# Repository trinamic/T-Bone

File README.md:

T-Bone
======
Electronic for up to 5 axes DIY desktop manufacturing platforms

LICENSE Files
=============
"LICENSE_HW" --> Attribution-ShareAlike 4.0 International license effective for the hardware part
"LICENSE_SW" --> agpl-3.0 license effective for the software part

"Software/ArduinoClient" Folder
===============================
The ArduinoClient folder  contains the Arduino software.

"Documentation/SoftwareDocumentation.pdf" File
==============================================
Documentation for the implemented protocol to communicate with the T-Bone via the UART interface.

"Documentation/T-bone_command_documentation.txt" File
=====================================================
Example file for the communication between Beagle Bone Black and the T-Bone (Arduino Leonardo)

Arduino Leonardo Pinout
=======================
Adapted from pins.h in the Arduino software.

Arduino Pin – Atmel Pin & function - connection

    D0 - PD2, RXD1/INT2 - Serial BeagleBone (UART1_TXD)
    D1 - PD3 TXD1/INT3 - Serial BeagleBone (UART1_RXD)
    D2 - PD1 SDA SDA/INT1 - Interrupt 4361 Nr.2
    D3# - PD0 PWM8/SCL OC0B/SCL/INT0 - Interrupt 4361 Nr.1
    D4 - A6 - PD4 ADC8 - CS 4361 Nr. 1
    D5# - PC6 ??? OC3A/#OC4A - PWM3, Fan
    D6# A7 - PD7 FastPWM #OC4D/ADC10 - CS 5031 Nr. 3
    D7 - PE6 INT6/AIN0 - Interrupt 4361 Nr.3
    D8 A8 - PB4 ADC11/PCINT4 - Interrupt 5041
    D9# A9 - PB5 PWM16 OC1A/#OC4B/ADC12/PCINT5 - PWM 1
    D10# A10 - PB6 PWM16 OC1B/0c4B/ADC13/PCINT6 - PWM 2
    D11# - PB7 PWM8/16 0C0A/OC1C/#RTS/PCINT7 - CS 5041
    D12 A11 - PD6 T1/#OC4D/ADC9 - CS 4361 Nr. 2
    D13# - PC7 PWM10 CLK0/OC4A - clock output do not use, never!
    A0 - D18 PF7 ADC7 - Temperature Sensor 1
    A1 - D19 PF6 ADC6 - Temperature Sensor 2
    A2 - D20 PF5 ADC5 - Temperature Sensor 3
    A3 - D21 PF4 ADC4 - Start Signal
    A4 - D22 PF1 ADC1 - Current PWM 1
    A5 - D23 PF0 ADC0 - Current PWM 2
    MISO - D14 PB3 MISO,PCINT3 - MISO
    SCK - D15 PB1 SCK,PCINT1 - SCK
    MOSI - D16 PB2 MOSI,PCINT2 - MOSI
    SS - D17 PB0 RXLED,SS/PCINT0 - RX LED
    TXLED - PD5 . TX LED
    HWB - PE2 HWB - Reset for motion drivers

"Software/ArduinoLibraries" Folder
==================================
This folder contains the used Arduino Libraries needed to compile the code.
!!Attention!!
The used libraries are standard ones, BUT customized. So be sure to use these!
!!Attention!!

For information on installing libraries, see: http://arduino.cc/en/Guide/Libraries

"Software/t_bone_server" Folder
===============================
This folder contains the software running on the Beagle Bone Black for the Deluxe version.

It's prepared to run a 3D-Printer Hardware. But can be customized to control different kind of desktop manufacturing platforms.

"Hardware/T-Bone Folder"
========================
Contains schematic and board design of the latest version of the T-Bone HW

"Hardware/Programming board" Folder
===================================
Contains schematic of a programming board adapter

"Hardware/BBQ" Folder
=====================
Contains schematic and board design for BBQ breakout board to evaluate TMC chipsets

"Hardware/TMC2100" Folder
=========================
Contains startup instructions for TMC2100 breakout board and schematics + board design

LJ

The T-Bone Team
2014

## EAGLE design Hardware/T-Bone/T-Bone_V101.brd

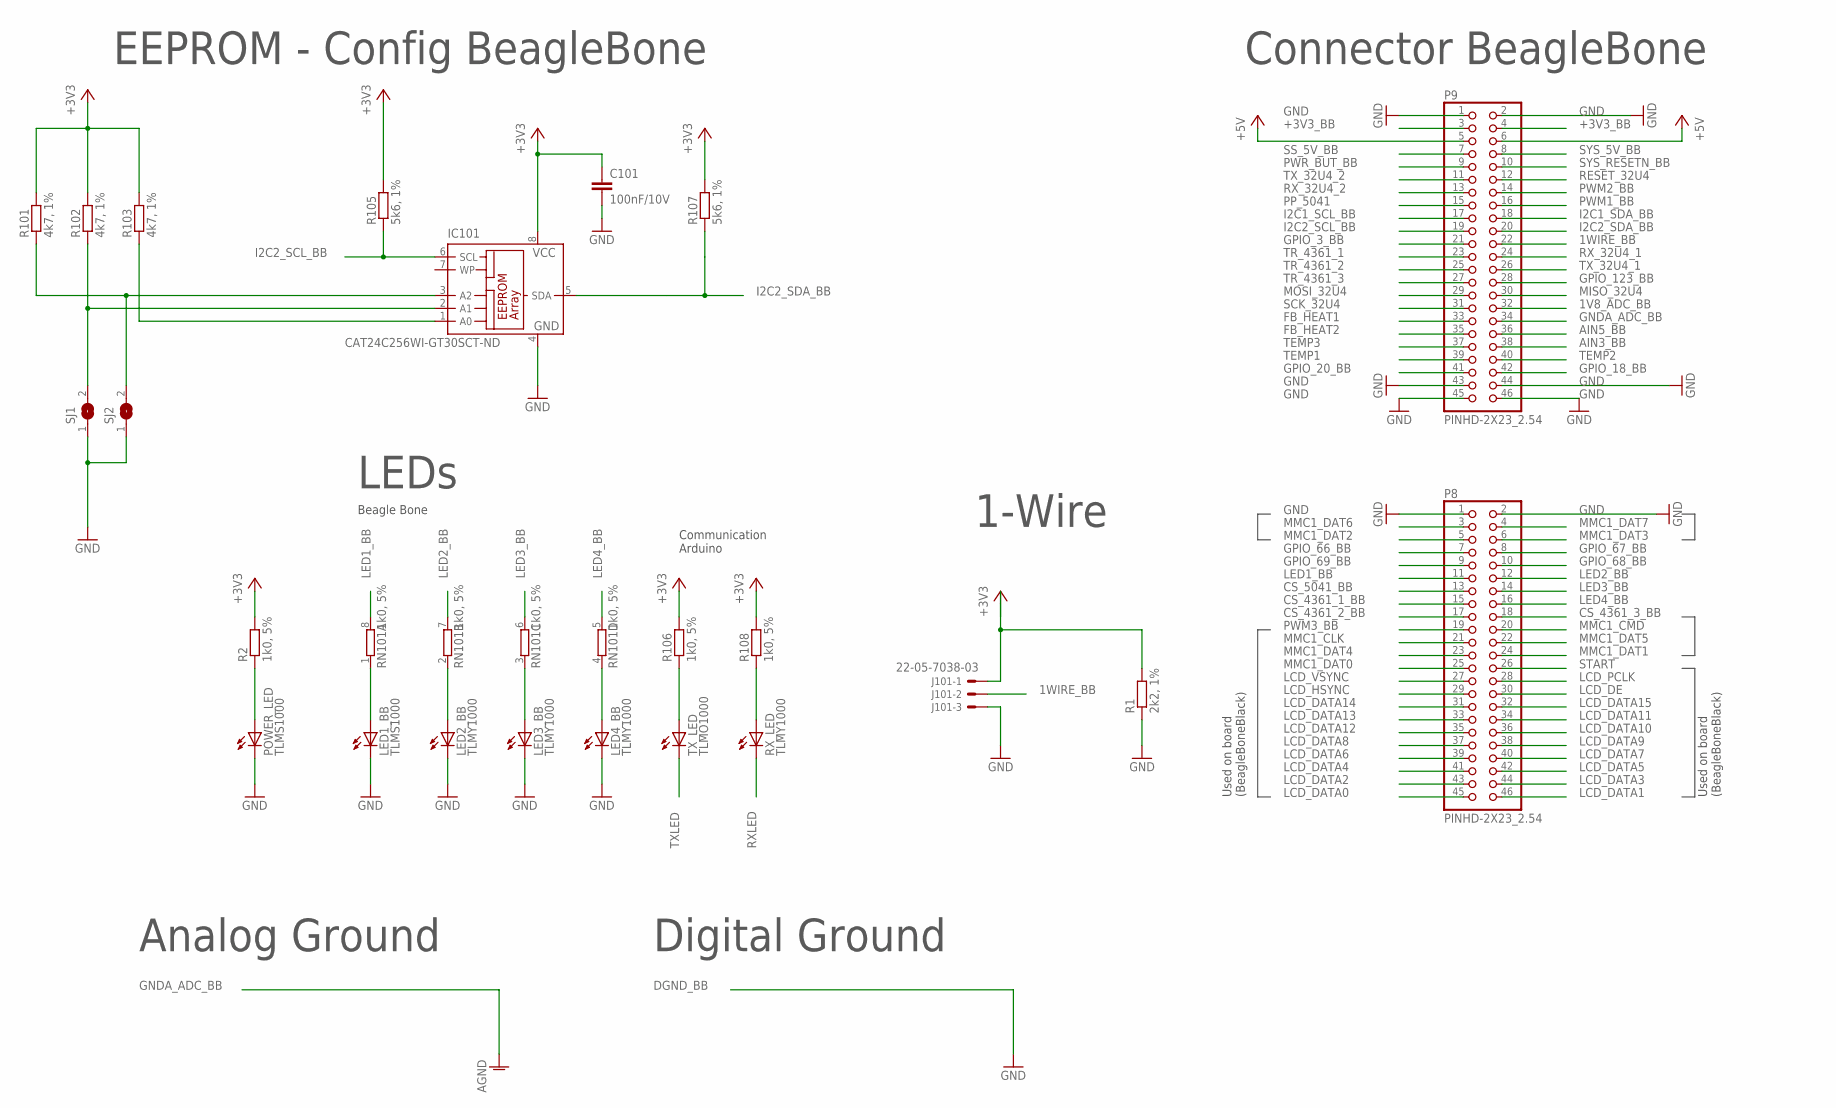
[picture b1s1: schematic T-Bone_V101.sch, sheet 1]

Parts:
C101: 100nF/10V; C0402K
IC101: CAT24C256WI-GT30SCT-ND; SO-08
J101: 22-05-7038-03; 7395-03
LED1_BB: TLMS1000; CHIP-LED0603
LED2_BB, LED3_BB, LED4_BB: TLMY1000; CHIP-LED0603
P8, P9: PINHD-2X23_2.54; 2X23
POWER_LED: TLMS1000; CHIP-LED0603
R1: 2k2, 1%; R0603
R2, R106, R108: 1k0, 5%; R0402
R101, R102, R103: 4k7, 1%; R0402
R105, R107: 5k6, 1%; R0402
RN101: 1k0, 5%; YC124
RX_LED: TLMY1000; CHIP-LED0603
SJ1, SJ2: SJ
TX_LED: TLMO1000; CHIP-LED0603

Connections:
1V8_ADC_BB: P9.32; also elsewhere on the board
1WIRE_BB: J101.2, P9.22
+3V3: C101.1, IC101.8 (VCC), J101.1, R1.2, R2.2, R101.2, R102.2, R103.2, R105.2, R106.2, R107.2, R108.2; also elsewhere on the board
+3V3_BB: P9.3, P9.4
+5V: P9.5, P9.6; also elsewhere on the board
AIN3_BB: P9.38
AIN5_BB: P9.36
CS_4361_1_BB: P8.15; also elsewhere on the board
CS_4361_2_BB: P8.17; also elsewhere on the board
CS_4361_3_BB: P8.18; also elsewhere on the board
CS_5041_BB: P8.13; also elsewhere on the board
FB_HEAT1: P9.33; also elsewhere on the board
FB_HEAT2: P9.35; also elsewhere on the board
GND: C101.2, IC101.4 (GND), J101.3, LED1_BB.C, LED2_BB.C, LED3_BB.C, LED4_BB.C, P8.1, P8.2, P9.1, P9.2, P9.43, P9.44, P9.45, P9.46, POWER_LED.C, R1.1, SJ1.1, SJ2.1; also elsewhere on the board
GNDA_ADC_BB: P9.34
GPIO_3_BB: P9.21
GPIO_18_BB: P9.42
GPIO_20_BB: P9.41
GPIO_66_BB: P8.7
GPIO_67_BB: P8.8
GPIO_68_BB: P8.10
GPIO_69_BB: P8.9
GPIO_123_BB: P9.28
I2C1_SCL_BB: P9.17
I2C1_SDA_BB: P9.18
I2C2_SCL_BB: IC101.6 (SCL), P9.19, R105.1
I2C2_SDA_BB: IC101.5 (SDA), P9.20, R107.1
LCD_DATA0: P8.45
LCD_DATA1: P8.46
LCD_DATA2: P8.43
LCD_DATA3: P8.44
LCD_DATA4: P8.41
LCD_DATA5: P8.42
LCD_DATA6: P8.39
LCD_DATA7: P8.40
LCD_DATA8: P8.37
LCD_DATA9: P8.38
LCD_DATA10: P8.36
LCD_DATA11: P8.34
LCD_DATA12: P8.35
LCD_DATA13: P8.33
LCD_DATA14: P8.31
LCD_DATA15: P8.32
LCD_DE: P8.30
LCD_HSYNC: P8.29
LCD_PCLK: P8.28
LCD_VSYNC: P8.27
LED1_BB: P8.11, RN101.8 (2)
LED2_BB: P8.12, RN101.7 (2)
LED3_BB: P8.14, RN101.6 (2)
LED4_BB: P8.16, RN101.5 (2)
MISO_32U4: P9.30; also elsewhere on the board
MMC1_CLK: P8.21
MMC1_CMD: P8.20
MMC1_DAT0: P8.25
MMC1_DAT1: P8.24
MMC1_DAT2: P8.5
MMC1_DAT3: P8.6
MMC1_DAT4: P8.23
MMC1_DAT5: P8.22
MMC1_DAT6: P8.3
MMC1_DAT7: P8.4
MOSI_32U4: P9.29; also elsewhere on the board
unnamed: R106.1, TX_LED.A
unnamed: R108.1, RX_LED.A
unnamed: POWER_LED.A, R2.1
unnamed: LED1_BB.A, RN101.1
unnamed: LED2_BB.A, RN101.2 (1)
unnamed: LED3_BB.A, RN101.3 (1)
unnamed: LED4_BB.A, RN101.4 (1)
unnamed: IC101.2 (A1), R102.1, SJ1.2
unnamed: IC101.1 (A0), R103.1
unnamed: IC101.3 (A2), R101.1, SJ2.2
PP_5041: P9.15; also elsewhere on the board
PWM1_BB: P9.16; also elsewhere on the board
PWM2_BB: P9.14; also elsewhere on the board
PWM3_BB: P8.19; also elsewhere on the board
PWR_BUT_BB: P9.9
RESET_32U4: P9.12; also elsewhere on the board
RXLED: RX_LED.C; also elsewhere on the board
RX_32U4_1: P9.24; also elsewhere on the board
RX_32U4_2: P9.13; also elsewhere on the board
SCK_32U4: P9.31; also elsewhere on the board
SS_5V_BB: P9.7
START: P8.26; also elsewhere on the board
SYS_5V_BB: P9.8
SYS_RESETN_BB: P9.10
TEMP1: P9.39; also elsewhere on the board
TEMP2: P9.40; also elsewhere on the board
TEMP3: P9.37; also elsewhere on the board
TR_4361_1: P9.23; also elsewhere on the board
TR_4361_2: P9.25; also elsewhere on the board
TR_4361_3: P9.27; also elsewhere on the board
TXLED: TX_LED.C; also elsewhere on the board
TX_32U4_1: P9.26; also elsewhere on the board
TX_32U4_2: P9.11; also elsewhere on the board

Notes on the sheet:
EEPROM - Config BeagleBone
Connector BeagleBone
Analog Ground
Digital Ground
LEDs
1-Wire
Communication Arduino
Beagle Bone
Used on board (BeagleBoneBlack)

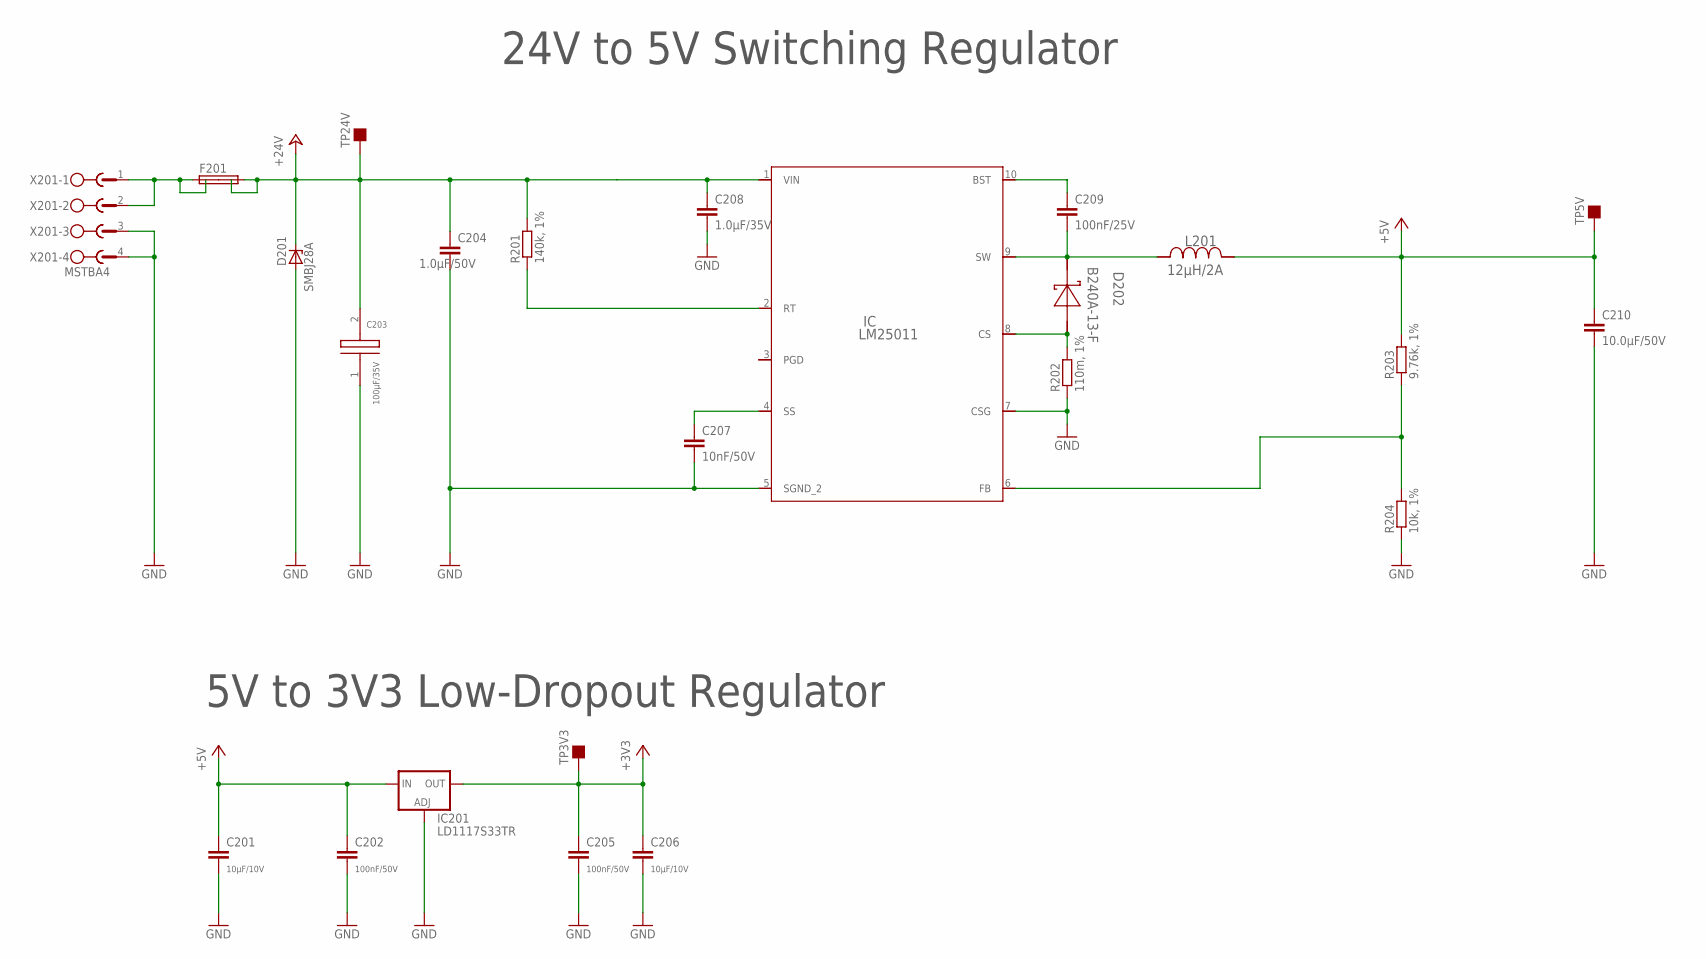
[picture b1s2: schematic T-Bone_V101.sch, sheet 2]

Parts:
C201, C206: 10µF/10V; C0805K
C202, C205: 100nF/50V; C0603K
C203: 100µF/35V; F
C204: 1.0µF/50V; C1206K
C207: 10nF/50V; C0805K
C208: 1.0µF/35V; C0805K
C209: 100nF/25V; C0805K
C210: 10.0µF/50V; C0603K
D201: SMBJ28A; SMB
D202: B240A-13-F; SMA
F201: SHK20Q
IC: LM25011; MUC10A
IC201: LD1117S33TR; SOT223
L201: 12µH/2A; SDR0805
R201: 140k, 1%; R0402
R202: 110m, 1%; R1210
R203: 9.76k, 1%; R0402
R204: 10k, 1%; R0402
TP3V3, TP5V, TP24V: TP
X201: MSTBA4

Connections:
24V_INPUT: F201.1A, F201.1B, X201.1, X201.2
+3V3: C205.1, C206.1, IC201.4 (OUT), TP3V3.P$1; also elsewhere on the board
+5V: C201.1, C202.1, C210.1, IC201.3 (IN), L201.1, R203.2, TP5V.P$1; also elsewhere on the board
+24V: C203.2, C204.1, C208.1, D201.C, F201.2A, F201.2B, IC.1 (VIN), R201.2, TP24V.P$1; also elsewhere on the board
GND: C201.2, C202.2, C203.1, C204.2, C205.2, C206.2, C207.2, C208.2, C210.2, D201.A, IC.5 (SGND_2), IC.7 (CSG), IC201.1 (ADJ), R202.1, R204.1, X201.3, X201.4; also elsewhere on the board
unnamed: D202.2 (A), IC.8 (CS), R202.2
unnamed: C209.2, D202.1 (K), IC.9 (SW), L201.2
unnamed: IC.6 (FB), R203.1, R204.2
unnamed: C209.1, IC.10 (BST)
unnamed: C207.1, IC.4 (SS)
unnamed: IC.2 (RT), R201.1

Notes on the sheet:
24V to 5V Switching Regulator
5V to 3V3 Low-Dropout Regulator

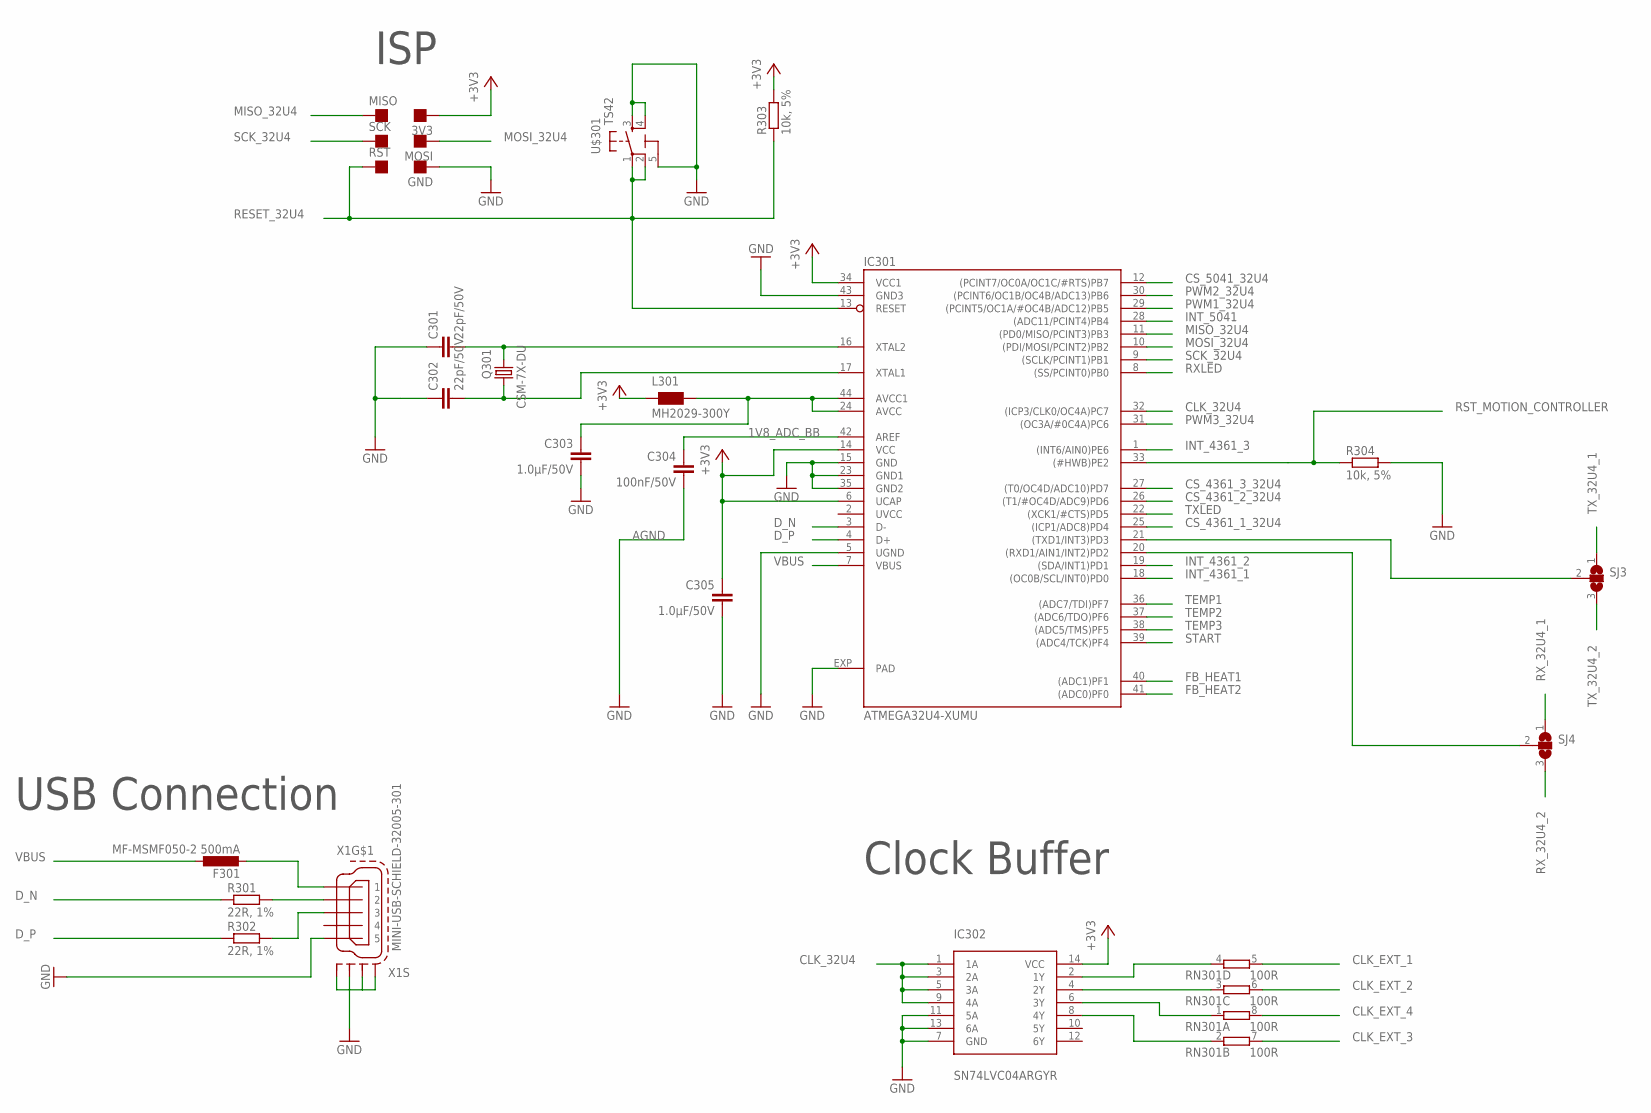
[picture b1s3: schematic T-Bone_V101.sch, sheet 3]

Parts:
3V3: TP
C301, C302: 22pF/50V; C0603K
C303, C305: 1.0µF/50V; C0603K
C304: 100nF/50V; C0603K
F301: MF-MSMF050-2 500mA; L1812
GND: TP
IC301: ATMEGA32U4-XUMU; QFN44ML7X7
IC302: SN74LVC04ARGYR; 14-VFQFN
L301: MH2029-300Y; 0805
MISO: TP
MOSI: TP
Q301: CSM-7X-DU
R301, R302: 22R, 1%; R0402
R303: 10k, 5%; R0603
R304: 10k, 5%; R0402
RN301: 100R; YC124
RST: TP
SCK: TP
SJ3, SJ4: SJ2W; SJ_2
U$301: TS42
X1: MINI-USB-SCHIELD-32005-301; 32005-301

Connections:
1V8_ADC_BB: C304.1, IC301.42 (AREF); also elsewhere on the board
+3V3: 3V3.P$1, C305.1, IC301.6 (UCAP), IC301.14 (VCC), IC301.34 (VCC1), IC302.14 (VCC), L301.1, R303.2; also elsewhere on the board
AGND: C304.2
CLK_32U4: IC301.32 ((ICP3/CLK0/OC4A)PC7), IC302.1 (1A), IC302.3 (2A), IC302.5 (3A), IC302.9 (4A)
CLK_EXT_1: RN301.5 (2); also elsewhere on the board
CLK_EXT_2: RN301.6 (2); also elsewhere on the board
CLK_EXT_3: RN301.7 (2); also elsewhere on the board
CLK_EXT_4: RN301.8 (2); also elsewhere on the board
CS_4361_1_32U4: IC301.25 ((ICP1/ADC8)PD4); also elsewhere on the board
CS_4361_2_32U4: IC301.26 ((T1/#OC4D/ADC9)PD6); also elsewhere on the board
CS_4361_3_32U4: IC301.27 ((T0/OC4D/ADC10)PD7); also elsewhere on the board
CS_5041_32U4: IC301.12 ((PCINT7/OC0A/OC1C/#RTS)PB7); also elsewhere on the board
D_N: IC301.3 (D-), R301.1
D_P: IC301.4 (D+), R302.1
FB_HEAT1: IC301.40 ((ADC1)PF1); also elsewhere on the board
FB_HEAT2: IC301.41 ((ADC0)PF0); also elsewhere on the board
GND: C301.1, C302.1, C303.2, C305.2, GND.P$1, IC301.5 (UGND), IC301.15 (GND), IC301.23 (GND1), IC301.35 (GND2), IC301.43 (GND3), IC301.EXP (PAD), IC302.7 (GND), IC302.11 (5A), IC302.13 (6A), R304.2, U$301.3, U$301.4, U$301.5 (5-GND), X1.5, X1.M1 (S1), X1.M2 (S2), X1.M3 (S3), X1.M4 (S4); also elsewhere on the board
INT_4361_1: IC301.18 ((OC0B/SCL/INT0)PD0); also elsewhere on the board
INT_4361_2: IC301.19 ((SDA/INT1)PD1); also elsewhere on the board
INT_4361_3: IC301.1 ((INT6/AIN0)PE6); also elsewhere on the board
INT_5041: IC301.28 ((ADC11/PCINT4)PB4); also elsewhere on the board
MISO_32U4: IC301.11 ((PD0/MISO/PCINT3)PB3), MISO.P$1; also elsewhere on the board
MOSI_32U4: IC301.10 ((PDI/MOSI/PCINT2)PB2), MOSI.P$1; also elsewhere on the board
unnamed: IC301.21 ((TXD1/INT3)PD3), SJ3.2
unnamed: R302.2, X1.3
unnamed: R301.2, X1.2
unnamed: IC302.6 (3Y), RN301.1
unnamed: IC302.8 (4Y), RN301.2 (1)
unnamed: IC302.2 (1Y), RN301.4 (1)
unnamed: C303.1, IC301.24 (AVCC), IC301.44 (AVCC1), L301.2
unnamed: IC302.4 (2Y), RN301.3 (1)
unnamed: F301.2, X1.1
unnamed: C301.2, IC301.16 (XTAL2), Q301.2
unnamed: C302.2, IC301.17 (XTAL1), Q301.1
unnamed: IC301.20 ((RXD1/AIN1/INT2)PD2), SJ4.2
PWM1_32U4: IC301.29 ((PCINT5/OC1A/#OC4B/ADC12)PB5); also elsewhere on the board
PWM2_32U4: IC301.30 ((PCINT6/OC1B/OC4B/ADC13)PB6); also elsewhere on the board
PWM3_32U4: IC301.31 ((OC3A/#0C4A)PC6); also elsewhere on the board
RESET_32U4: IC301.13 (RESET), R303.1, RST.P$1, U$301.1, U$301.2; also elsewhere on the board
RST_MOTION_CONTROLLER: IC301.33 ((#HWB)PE2), R304.1; also elsewhere on the board
RXLED: IC301.8 ((SS/PCINT0)PB0); also elsewhere on the board
RX_32U4_1: SJ4.1; also elsewhere on the board
RX_32U4_2: SJ4.3; also elsewhere on the board
SCK_32U4: IC301.9 ((SCLK/PCINT1)PB1), SCK.P$1; also elsewhere on the board
START: IC301.39 ((ADC4/TCK)PF4); also elsewhere on the board
TEMP1: IC301.36 ((ADC7/TDI)PF7); also elsewhere on the board
TEMP2: IC301.37 ((ADC6/TDO)PF6); also elsewhere on the board
TEMP3: IC301.38 ((ADC5/TMS)PF5); also elsewhere on the board
TXLED: IC301.22 ((XCK1/#CTS)PD5); also elsewhere on the board
TX_32U4_1: SJ3.1; also elsewhere on the board
TX_32U4_2: SJ3.3; also elsewhere on the board
UVCC: IC301.2 (UVCC)
VBUS: F301.1, IC301.7 (VBUS)

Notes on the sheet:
ISP
USB Connection
Clock Buffer

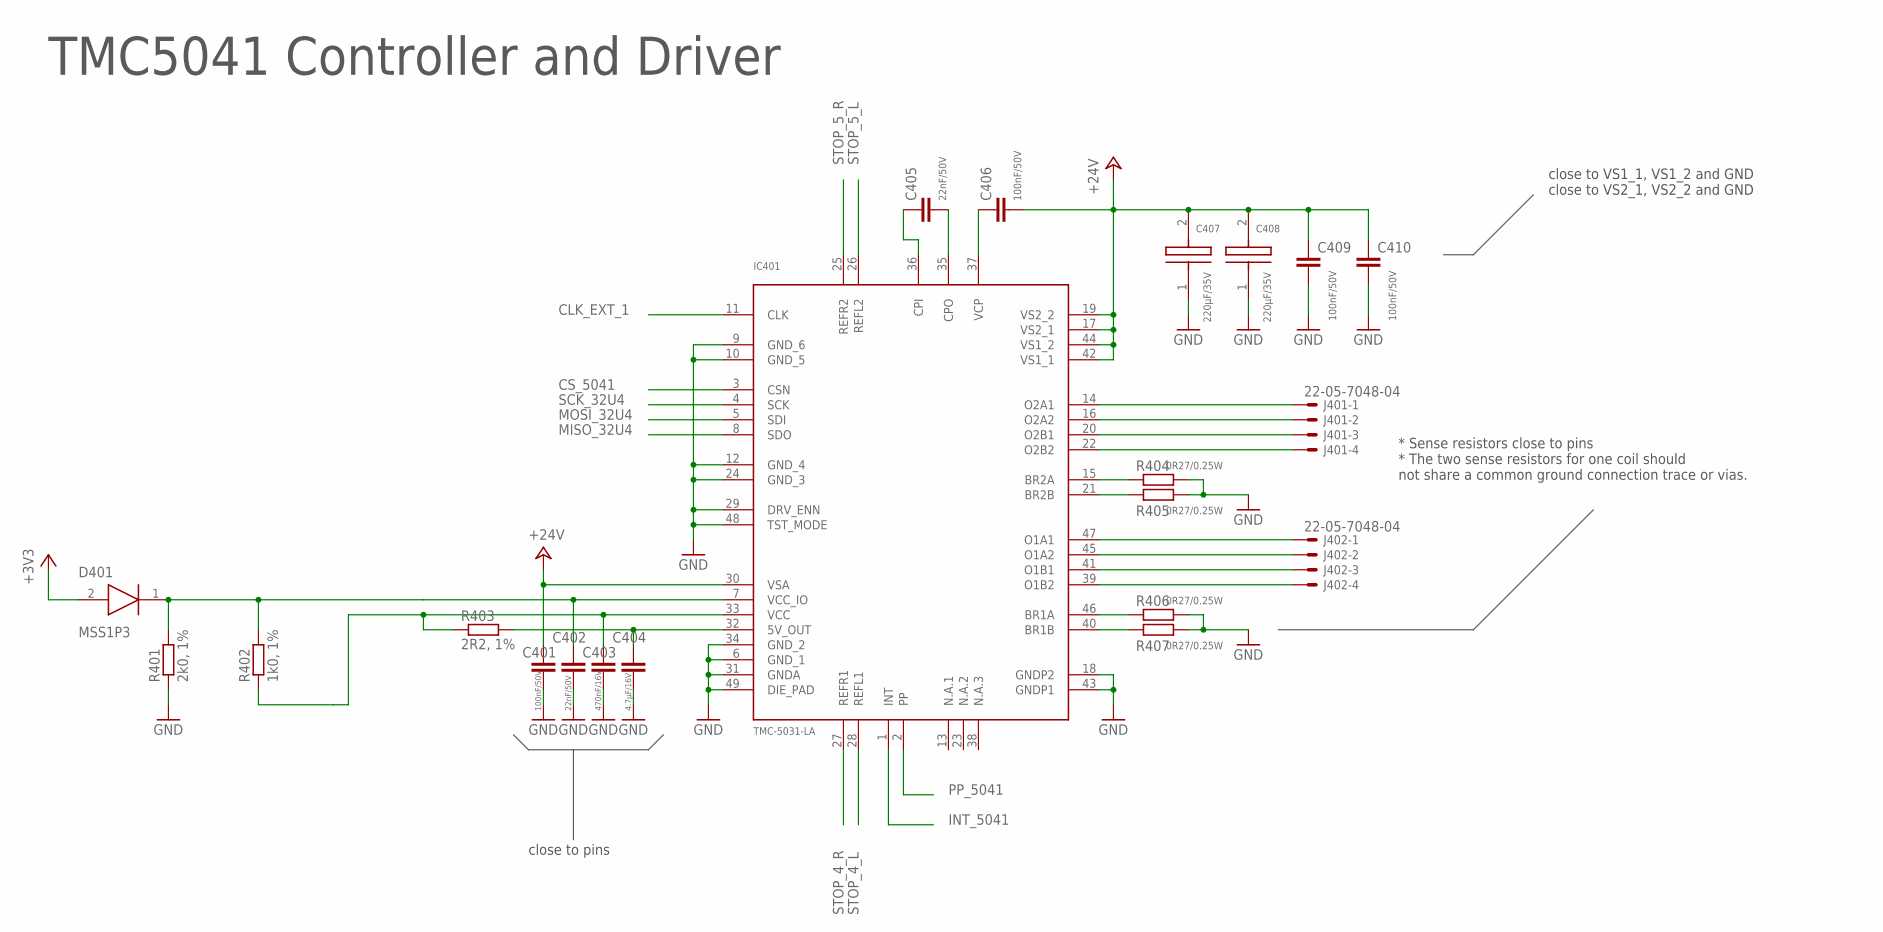
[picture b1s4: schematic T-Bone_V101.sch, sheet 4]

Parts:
C401, C406, C409, C410: 100nF/50V; C0603K
C402, C405: 22nF/50V; C0603K
C403: 470nF/16V; C0603K
C404: 4.7µF/16V; C0603K
C407, C408: 220µF/35V; F
D401: MSS1P3; MSS1PX
IC401: TMC-5031-LA; QFN48
J401, J402: 22-05-7048-04; 7395-04
R401: 2k0, 1%; R0603
R402: 1k0, 1%; R0603
R403: 2R2, 1%; R0603
R404, R405, R406, R407: 0R27/0.25W; R1206

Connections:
5031_O1A1: IC401.47 (O1A1), J402.1
5031_O1A2: IC401.45 (O1A2), J402.2
5031_O1B1: IC401.41 (O1B1), J402.3
5031_O1B2: IC401.39 (O1B2), J402.4
5031_O2A1: IC401.14 (O2A1), J401.1
5031_O2A2: IC401.16 (O2A2), J401.2
5031_O2B1: IC401.20 (O2B1), J401.3
5031_O2B2: IC401.22 (O2B2), J401.4
+3V3: D401.2 (ANODE); also elsewhere on the board
+24V: C401.1, C406.2, C407.2, C408.2, C409.1, C410.1, IC401.17 (VS2_1), IC401.19 (VS2_2), IC401.30 (VSA), IC401.42 (VS1_1), IC401.44 (VS1_2); also elsewhere on the board
CLK_EXT_1: IC401.11 (CLK); also elsewhere on the board
CS_5041: IC401.3 (CSN); also elsewhere on the board
GND: C401.2, C402.2, C403.2, C404.2, C407.1, C408.1, C409.2, C410.2, IC401.6 (GND_1), IC401.9 (GND_6), IC401.10 (GND_5), IC401.12 (GND_4), IC401.18 (GNDP2), IC401.24 (GND_3), IC401.29 (DRV_ENN), IC401.31 (GNDA), IC401.34 (GND_2), IC401.43 (GNDP1), IC401.48 (TST_MODE), IC401.49 (DIE_PAD), R401.1, R404.2, R405.2, R406.2, R407.2; also elsewhere on the board
INT_5041: IC401.1 (INT); also elsewhere on the board
MISO_32U4: IC401.8 (SDO); also elsewhere on the board
MOSI_32U4: IC401.5 (SDI); also elsewhere on the board
unnamed: C403.1, IC401.33 (VCC), R402.1, R403.1
unnamed: C405.2, IC401.35 (CPO)
unnamed: C405.1, IC401.36 (CPI)
unnamed: C406.1, IC401.37 (VCP)
unnamed: C404.1, IC401.32 (5V_OUT), R403.2
unnamed: IC401.21 (BR2B), R405.1
unnamed: IC401.15 (BR2A), R404.1
unnamed: IC401.40 (BR1B), R407.1
unnamed: IC401.46 (BR1A), R406.1
unnamed: C402.1, D401.1 (KATHODE), IC401.7 (VCC_IO), R401.2, R402.2
PP_5041: IC401.2 (PP); also elsewhere on the board
SCK_32U4: IC401.4 (SCK); also elsewhere on the board
STOP_4_L: IC401.28 (REFL1); also elsewhere on the board
STOP_4_R: IC401.27 (REFR1); also elsewhere on the board
STOP_5_L: IC401.26 (REFL2); also elsewhere on the board
STOP_5_R: IC401.25 (REFR2); also elsewhere on the board

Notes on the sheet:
TMC5041 Controller and Driver
close to VS1_1, VS1_2 and GND close to VS2_1, VS2_2 and GND
close to pins
* Sense resistors close to pins * The two sense resistors for one coil should not share a common ground connection trace or vias.

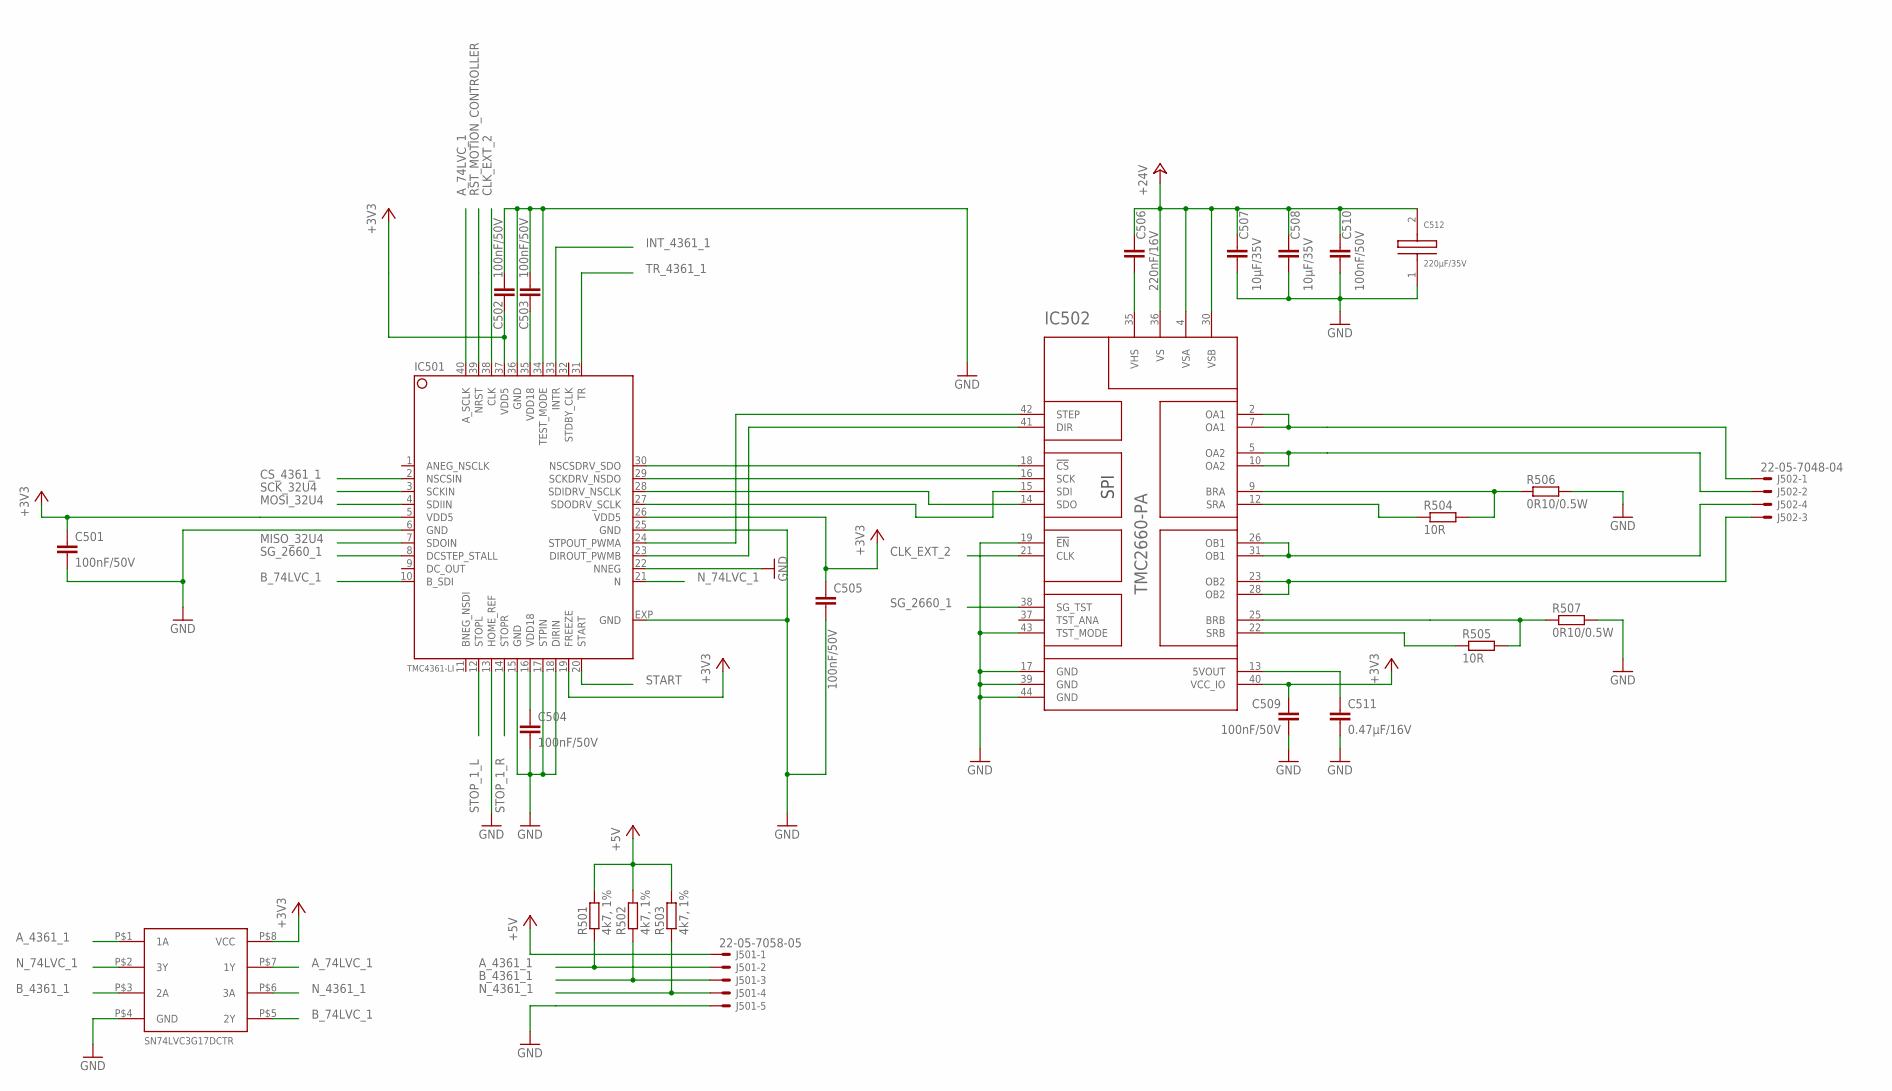
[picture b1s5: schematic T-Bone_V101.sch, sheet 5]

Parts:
C501, C502, C503, C504, C505, C509, C510: 100nF/50V; C0603K
C506: 220nF/16V; C0603K
C507, C508: 10µF/35V; C1210K
C511: 0.47µF/16V; C0603K
C512: 220µF/35V; F
IC501: TMC4361-LI; QFN40L
IC502: TMC2660-PA; PQFP44_WITH_PADS
J501: 22-05-7058-05; 7395-05
J502: 22-05-7048-04; 7395-04
R501, R502, R503: 4k7, 1%; R0603
R504, R505: 10R; R0603
R506, R507: 0R10/0.5W; R1206
U$501: SN74LVC3G17-SM8

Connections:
+3V3: C501.1, C502.2, C505.1, C509.1, IC501.5 (VDD5), IC501.19 (FREEZE), IC501.26 (VDD5), IC501.37 (VDD5), IC502.40 (VCC_IO), U$501.P$8 (VCC); also elsewhere on the board
+5V: J501.1, R501.2, R502.2, R503.2; also elsewhere on the board
+24V: C506.1, C507.1, C508.1, C510.1, C512.2, IC502.4 (VSA), IC502.30 (VSB), IC502.36 (VS); also elsewhere on the board
A_74LVC_1: IC501.40 (A_SCLK), U$501.P$7 (1Y)
A_4361_1: J501.2, R501.1, U$501.P$1 (1A)
B_74LVC_1: IC501.10 (B_SDI), U$501.P$5 (2Y)
B_4361_1: J501.3, R502.1, U$501.P$3 (2A)
CLK_EXT_2: IC501.38 (CLK), IC502.21 (CLK); also elsewhere on the board
CS_4361_1: IC501.2 (NSCSIN); also elsewhere on the board
GND: C501.2, C502.1, C503.1, C504.2, C505.2, C507.2, C508.2, C509.2, C510.2, C511.2, C512.1, IC501.6 (GND), IC501.13 (HOME_REF), IC501.15 (GND), IC501.17 (STPIN), IC501.18 (DIRIN), IC501.22 (NNEG), IC501.25 (GND), IC501.34 (TEST_MODE), IC501.36 (GND), IC501.EXP (GND), IC502.17 (GND), IC502.19 (!EN), IC502.39 (GND), IC502.43 (TST_MODE), IC502.44 (GND), J501.5, R506.2, R507.2, U$501.P$4 (GND); also elsewhere on the board
IC502_OA1: IC502.2 (OA1), IC502.7 (OA1), J502.1
IC502_OA2: IC502.5 (OA2), IC502.10 (OA2), J502.2
IC502_OB1: IC502.26 (OB1), IC502.31 (OB1), J502.4
IC502_OB2: IC502.23 (OB2), IC502.28 (OB2), J502.3
INT_4361_1: IC501.33 (INTR); also elsewhere on the board
MISO_32U4: IC501.7 (SDOIN); also elsewhere on the board
MOSI_32U4: IC501.4 (SDIIN); also elsewhere on the board
unnamed: IC501.28 (SDIDRV_NSCLK), IC502.14 (SDO)
unnamed: IC501.27 (SDODRV_SCLK), IC502.15 (SDI)
unnamed: IC501.29 (SCKDRV_NSDO), IC502.16 (SCK)
unnamed: IC501.30 (NSCSDRV_SDO), IC502.18 (!CS)
unnamed: C511.1, IC502.13 (5VOUT)
unnamed: C506.2, IC502.35 (VHS)
unnamed: IC502.22 (SRB), R505.1
unnamed: IC502.25 (BRB), R505.2, R507.1
unnamed: IC502.12 (SRA), R504.1
unnamed: IC502.9 (BRA), R504.2, R506.1
unnamed: IC501.24 (STPOUT_PWMA), IC502.42 (STEP)
unnamed: IC501.23 (DIROUT_PWMB), IC502.41 (DIR)
unnamed: C503.2, IC501.35 (VDD18)
unnamed: C504.1, IC501.16 (VDD18)
N_74LVC_1: IC501.21 (N), U$501.P$2 (3Y)
N_4361_1: J501.4, R503.1, U$501.P$6 (3A)
RST_MOTION_CONTROLLER: IC501.39 (NRST); also elsewhere on the board
SCK_32U4: IC501.3 (SCKIN); also elsewhere on the board
SG_2660_1: IC501.8 (DCSTEP_STALL), IC502.38 (SG_TST)
START: IC501.20 (START); also elsewhere on the board
STOP_1_L: IC501.12 (STOPL); also elsewhere on the board
STOP_1_R: IC501.14 (STOPR); also elsewhere on the board
TR_4361_1: IC501.31 (TR); also elsewhere on the board

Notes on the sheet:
SN74LVC3G17DCTR

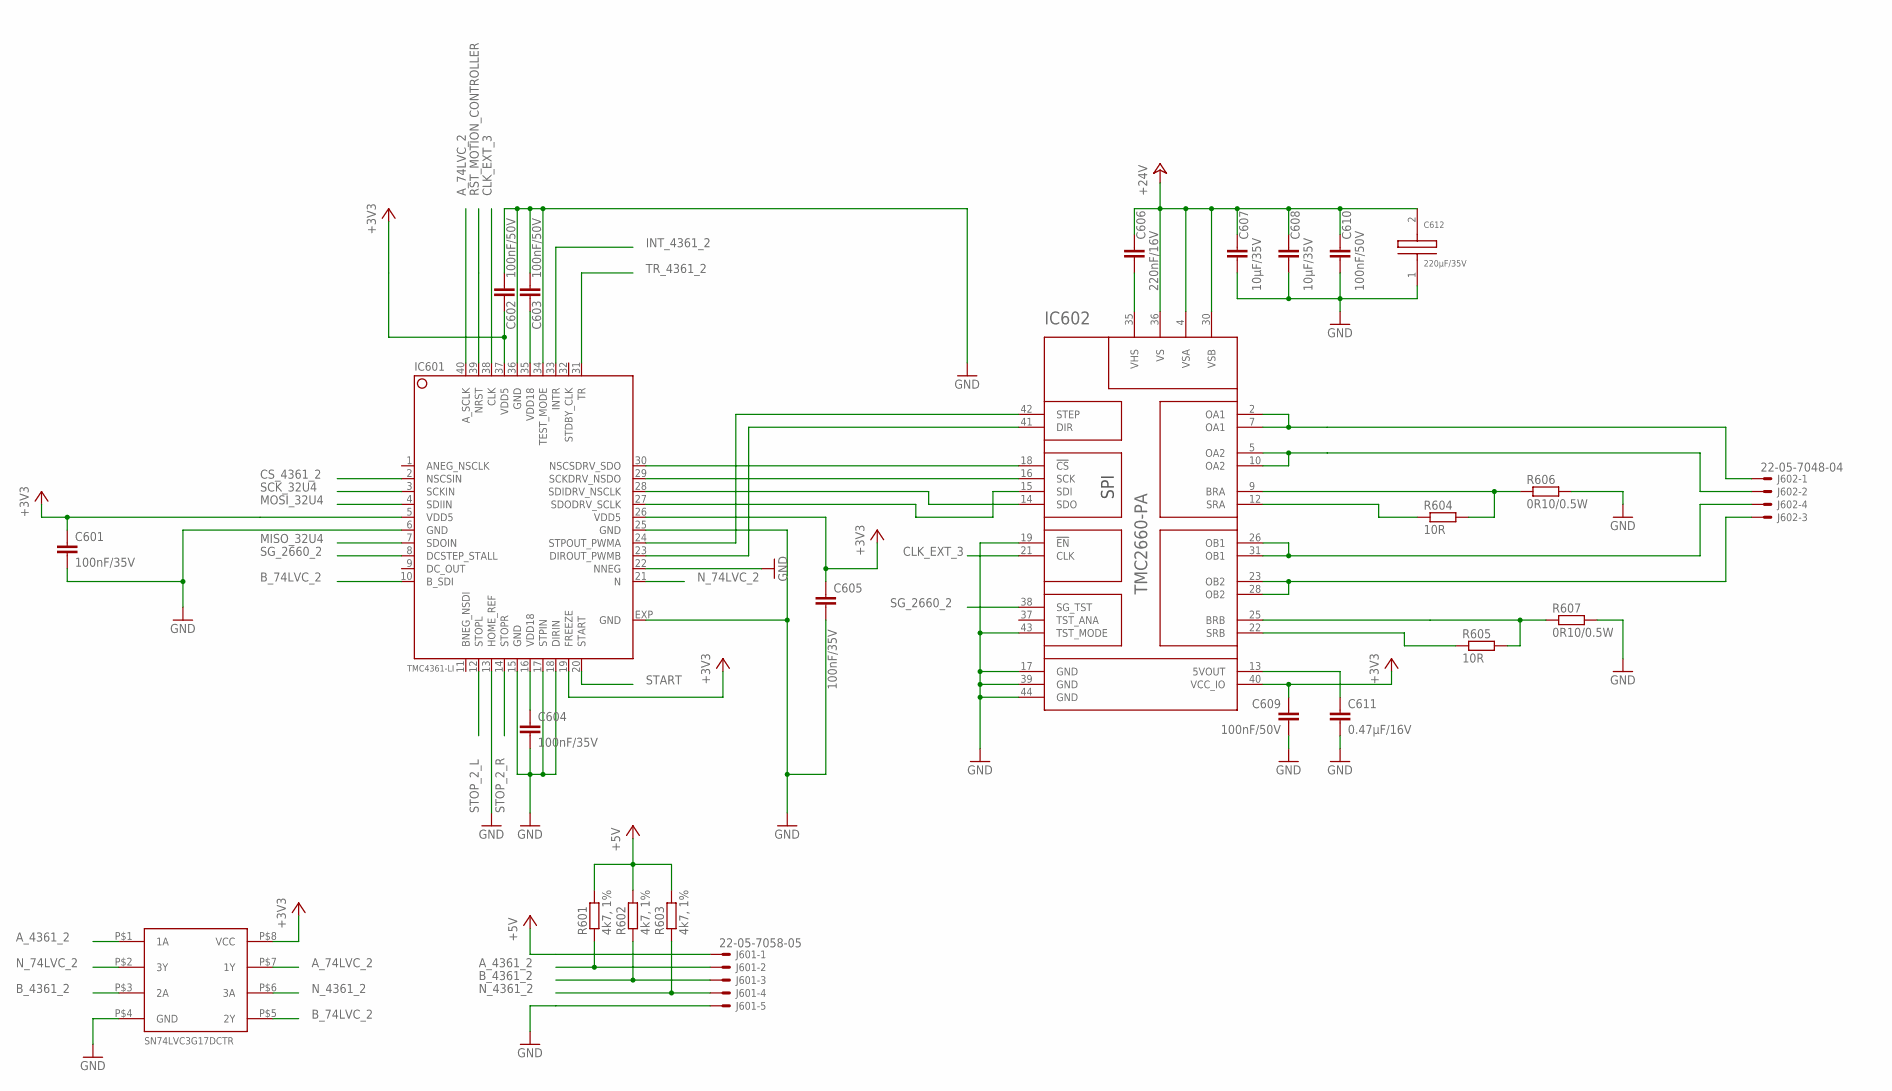
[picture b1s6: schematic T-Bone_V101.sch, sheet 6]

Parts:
C601, C604, C605: 100nF/35V; C0603K
C602, C603, C609, C610: 100nF/50V; C0603K
C606: 220nF/16V; C0603K
C607, C608: 10µF/35V; C1210K
C611: 0.47µF/16V; C0603K
C612: 220µF/35V; F
IC601: TMC4361-LI; QFN40L
IC602: TMC2660-PA; PQFP44_WITH_PADS
J601: 22-05-7058-05; 7395-05
J602: 22-05-7048-04; 7395-04
R601, R602, R603: 4k7, 1%; R0603
R604, R605: 10R; R0603
R606, R607: 0R10/0.5W; R1206
U$601: SN74LVC3G17-SM8

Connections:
+3V3: C601.1, C602.2, C605.1, C609.1, IC601.5 (VDD5), IC601.19 (FREEZE), IC601.26 (VDD5), IC601.37 (VDD5), IC602.40 (VCC_IO), U$601.P$8 (VCC); also elsewhere on the board
+5V: J601.1, R601.2, R602.2, R603.2; also elsewhere on the board
+24V: C606.1, C607.1, C608.1, C610.1, C612.2, IC602.4 (VSA), IC602.30 (VSB), IC602.36 (VS); also elsewhere on the board
A_74LVC_2: IC601.40 (A_SCLK), U$601.P$7 (1Y)
A_4361_2: J601.2, R601.1, U$601.P$1 (1A)
B_74LVC_2: IC601.10 (B_SDI), U$601.P$5 (2Y)
B_4361_2: J601.3, R602.1, U$601.P$3 (2A)
CLK_EXT_3: IC601.38 (CLK), IC602.21 (CLK); also elsewhere on the board
CS_4361_2: IC601.2 (NSCSIN); also elsewhere on the board
GND: C601.2, C602.1, C603.1, C604.2, C605.2, C607.2, C608.2, C609.2, C610.2, C611.2, C612.1, IC601.6 (GND), IC601.13 (HOME_REF), IC601.15 (GND), IC601.17 (STPIN), IC601.18 (DIRIN), IC601.22 (NNEG), IC601.25 (GND), IC601.34 (TEST_MODE), IC601.36 (GND), IC601.EXP (GND), IC602.17 (GND), IC602.19 (!EN), IC602.39 (GND), IC602.43 (TST_MODE), IC602.44 (GND), J601.5, R606.2, R607.2, U$601.P$4 (GND); also elsewhere on the board
IC602_OA1: IC602.2 (OA1), IC602.7 (OA1), J602.1
IC602_OA2: IC602.5 (OA2), IC602.10 (OA2), J602.2
IC602_OB1: IC602.26 (OB1), IC602.31 (OB1), J602.4
IC602_OB2: IC602.23 (OB2), IC602.28 (OB2), J602.3
INT_4361_2: IC601.33 (INTR); also elsewhere on the board
MISO_32U4: IC601.7 (SDOIN); also elsewhere on the board
MOSI_32U4: IC601.4 (SDIIN); also elsewhere on the board
unnamed: IC601.28 (SDIDRV_NSCLK), IC602.14 (SDO)
unnamed: IC601.27 (SDODRV_SCLK), IC602.15 (SDI)
unnamed: IC601.29 (SCKDRV_NSDO), IC602.16 (SCK)
unnamed: IC602.9 (BRA), R604.2, R606.1
unnamed: IC602.12 (SRA), R604.1
unnamed: IC601.30 (NSCSDRV_SDO), IC602.18 (!CS)
unnamed: C606.2, IC602.35 (VHS)
unnamed: IC601.24 (STPOUT_PWMA), IC602.42 (STEP)
unnamed: IC601.23 (DIROUT_PWMB), IC602.41 (DIR)
unnamed: C611.1, IC602.13 (5VOUT)
unnamed: IC602.25 (BRB), R605.2, R607.1
unnamed: IC602.22 (SRB), R605.1
unnamed: C603.2, IC601.35 (VDD18)
unnamed: C604.1, IC601.16 (VDD18)
N_74LVC_2: IC601.21 (N), U$601.P$2 (3Y)
N_4361_2: J601.4, R603.1, U$601.P$6 (3A)
RST_MOTION_CONTROLLER: IC601.39 (NRST); also elsewhere on the board
SCK_32U4: IC601.3 (SCKIN); also elsewhere on the board
SG_2660_2: IC601.8 (DCSTEP_STALL), IC602.38 (SG_TST)
START: IC601.20 (START); also elsewhere on the board
STOP_2_L: IC601.12 (STOPL); also elsewhere on the board
STOP_2_R: IC601.14 (STOPR); also elsewhere on the board
TR_4361_2: IC601.31 (TR); also elsewhere on the board

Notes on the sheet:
SN74LVC3G17DCTR

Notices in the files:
Hardware/T-Bone/T-Bone_V101.brd:
CC BY-SA 4.0
